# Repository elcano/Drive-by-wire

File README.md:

# DriveByWire

Obsolete. New code is in DBW version 5.

This repository is for use with the **Drive by Wire** board created to be used for the ELCANO self-driving tricycle. In order for this module to run external libraries are required.

Repositories were updated 6/8/2023 but clobbered previous history. Chief addition is use of an RC controller that allows manual control of throttle, brakes and steering.
The Sender files are intended for use on the Hi-Level board and do not really belong in the Drive-by-wire repository.

Libraries needed are listed below:

ALL Versions ________________________________
* PID by Brett Beauregard
    https://github.com/br3ttb/Arduino-PID-Library
    A simple controller calculator (proportional integral derivative) to calculate the error between a desired output and an actual output. Has files **PID_v1**

Version 3 (Arduino Mega) ________________________________
* CAN_BUS_SHIELD by Seeed-Studio
    https://github.com/Seeed-Studio/CAN_BUS_Shield
    Contains CAN_BUS communication protocols and required files such as **mcp_can** and **can-serial**

* Pin Change Interrupt by Nico Hood
    https://github.com/NicoHood/PinChangeInterrupt
    For custom configuration of Arduino pin properties. Has files **PinChangeInterupt**

* MCP48x2 DAC by Jonas Forsberg
    https://github.com/SweBarre/MCP48x2.
    Library for Digital to anolog converter. Has files **MCP48x2**

Version 4 (Arduino Due)  _______________________________________________
* Due CAN and CAN Common by Collin Kidder
    https://github.com/collin80/due_can
    https://github.com/collin80/can_common

## To Install

* Download the **Drive_By_Wire** module into the project parent directory
```
git clone https://github.com/elcano/Drive-by-wire.git
```
* Move into the **Drive_By_Wire** folder
```
cd Drive_By_Wire
```
* Download the required libraries
```
git clone https://github.com/Seeed-Studio/Seeed_Arduino_CAN.git
git clone https://github.com/br3ttb/Arduino-PID-Library.git
git clone https://github.com/NicoHood/PinChangeInterrupt.git
git clone https://github.com/SweBarre/MCP48x2.git
git clone https://github.com/ivanseidel/DueTimer.git
git clone https://github.com/collin80/can_common.git
git clone https://github.com/collin80/due_can.git
```
* Add the folders above to the IDE directory. In Windows, add the required libraries to: C:\Users\<username>\Documents\Arduino\libraries
* Arduino Due requires additional installation. On the IDE, go to Tools -> Boards -> Boards Manager -> Arduino SAM Boards (32-bits ARM Cortex-M3) 

## Navigating Arduino IDE: 
* **Selecting Board:** Tools -> Board -> Arduino AVR/SAM Boards -> Arduino Mega/Due
* **Selecting Serial Port:** Tools -> Port -> COM (Arduino Mega/Due)
* **Accessing Serial Monitor:** Right-hand Corner -> Select Baud Rate (115200)

## Drive-by-Wire: 
* **Low-level board code with RC control support with existing code for brakes, steering, and throttle.** 

## Test: 
* **Low-level board code with three functions to test each subsystems individually (brakes, steering, throttle).** 
* testBrake(): Activates brakes with 24V via Stop(), Holds brakes with 12V after 800ms via Update(), Releases brakes every ~2 seconds.
* testThrottle(): Gradually increases speed and decreases speed on DACA.
* testSteering(): Changes directions every 3 seconds, moving the linear actuator. 

## Sender: 
* **High-level board code to communicate with low-level board using CAN communication.** 
* Arguments for Function: Each data is reserved for 2 bytes. 
    *   currentSpeed: Controls the speed via the DACA, input: (0 -255).
    *   currentBrake: Apply and updates brakes if necessary, input: (0 - releases brakes, anything above 0 - applies brakes).
    *   currentAngle: Changes direction based on input (may need to calibrate based on sensors), left: 779 (1ms), middle: 722 (1.5ms), right: 639 (1.85ms).

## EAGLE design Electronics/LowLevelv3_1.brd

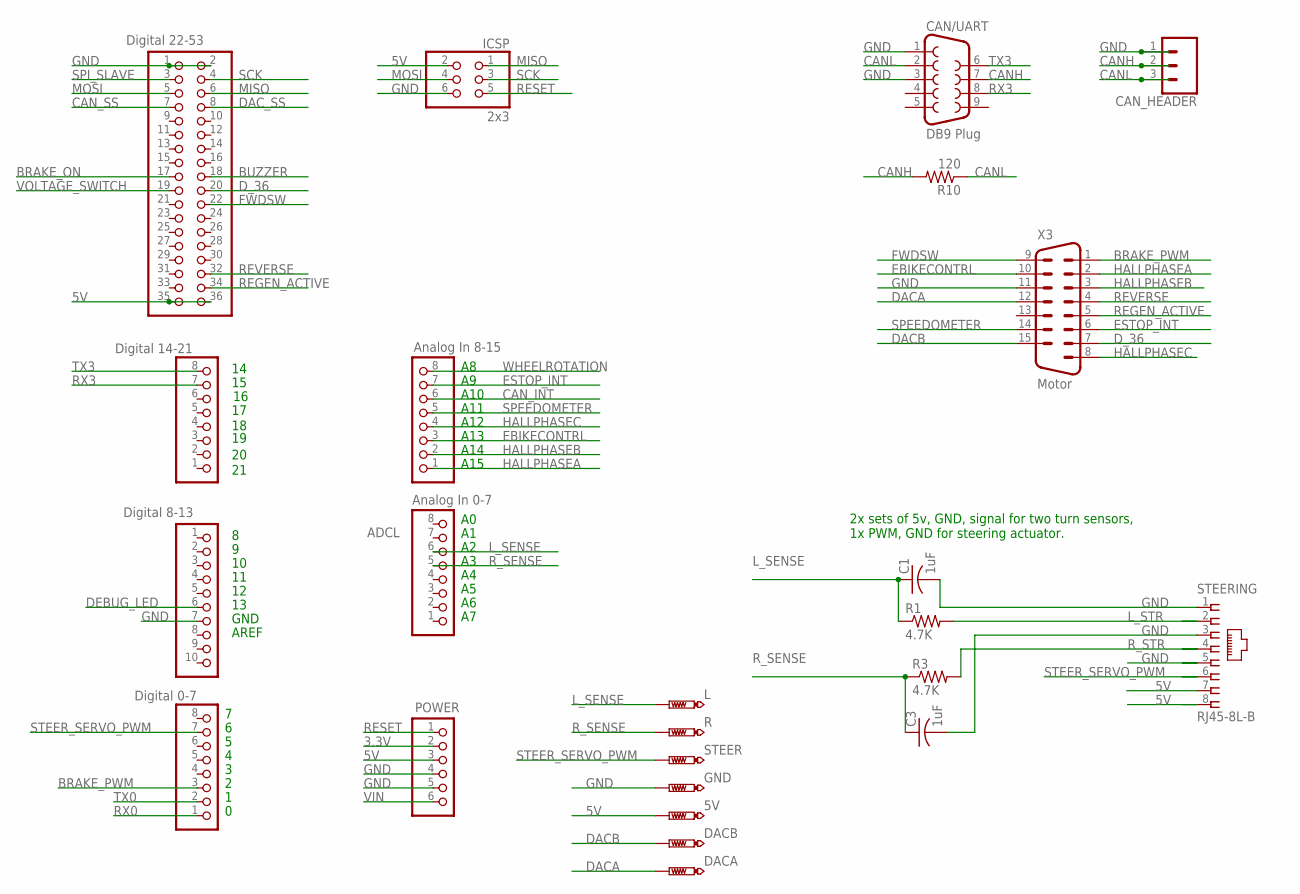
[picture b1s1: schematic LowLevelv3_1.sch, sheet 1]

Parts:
5V: PTR1PAD1-17; P1-17
ADCH: Analog In 8-15; 1X08
ADCL: Analog In 0-7; 1X08
C1, C3: 1uF; C1206
CAN/UART: DB9 Plug; DB9
CAN_HEADER: CONN_03-SCREW-5MM; SCREWTERMINAL-5MM-3
DACA: PTR1PAD1-17; P1-17
DACB: PTR1PAD1-17; P1-17
DIGITAL_0-7: Digital 0-7; 1X08
DIGITAL_8-13: Digital 8-13; 1X10
DIGITAL_14-21: Digital 14-21; 1X08
GND: PTR1PAD1-17; P1-17
ICSP: 2x3; 2X03
L: PTR1PAD1-17; P1-17
MEGA_EXPANSION: Digital 22-53; PINHEAD_2X18
POWER: PINHD-1X6; 1X06
R: PTR1PAD1-17; P1-17
R1, R3: 4.7K; R1206
R10: 120; R1206
STEER: PTR1PAD1-17; P1-17
STEERING: RJ45-8L-B; RJ45-NO-SHIELD
X3: Motor; 182-015-MALE

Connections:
3.3V: POWER.2
5V: 5V.TP, ICSP.2, MEGA_EXPANSION.35, MEGA_EXPANSION.36, POWER.3, STEERING.7, STEERING.8; also elsewhere on the board
BRAKE_ON: MEGA_EXPANSION.17; also elsewhere on the board
BRAKE_PWM: DIGITAL_0-7.3, X3.1
BUZZER: MEGA_EXPANSION.18; also elsewhere on the board
CANH: CAN/UART.7, CAN_HEADER.2, R10.2; also elsewhere on the board
CANL: CAN/UART.2, CAN_HEADER.3, R10.1; also elsewhere on the board
CAN_INT: ADCH.6; also elsewhere on the board
CAN_SS: MEGA_EXPANSION.7; also elsewhere on the board
DACA: DACA.TP, X3.12; also elsewhere on the board
DACB: DACB.TP, X3.15; also elsewhere on the board
DAC_SS: MEGA_EXPANSION.8; also elsewhere on the board
DEBUG_LED: DIGITAL_8-13.6; also elsewhere on the board
D_36: MEGA_EXPANSION.20, X3.7
EBIKECONTRL: ADCH.3, X3.10
ESTOP_INT: ADCH.7, X3.6; also elsewhere on the board
FWDSW: MEGA_EXPANSION.22, X3.9
GND: C1.2, C3.2, CAN/UART.1, CAN/UART.3, CAN_HEADER.1, DIGITAL_8-13.7, GND.TP, ICSP.6, MEGA_EXPANSION.1, MEGA_EXPANSION.2, POWER.4, POWER.5, STEERING.1, STEERING.3, STEERING.5, X3.11; also elsewhere on the board
HALLPHASEA: ADCH.1, X3.2
HALLPHASEB: ADCH.2, X3.3
HALLPHASEC: ADCH.4, X3.8
L_SENSE: ADCL.6, C1.1, L.TP, R1.1
L_STR: R1.2, STEERING.2
MISO: ICSP.1, MEGA_EXPANSION.6; also elsewhere on the board
MOSI: ICSP.4, MEGA_EXPANSION.5; also elsewhere on the board
REGEN_ACTIVE: MEGA_EXPANSION.34, X3.5
RESET: ICSP.5, POWER.1; also elsewhere on the board
REVERSE: MEGA_EXPANSION.32, X3.4
RX0: DIGITAL_0-7.1
RX3: CAN/UART.8, DIGITAL_14-21.7
R_SENSE: ADCL.5, C3.1, R.TP, R3.1
R_STR: R3.2, STEERING.4
SCK: ICSP.3, MEGA_EXPANSION.4; also elsewhere on the board
SPEEDOMETER: ADCH.5, X3.14
SPI_SLAVE: MEGA_EXPANSION.3
STEER_SERVO_PWM: DIGITAL_0-7.7, STEER.TP, STEERING.6
TX0: DIGITAL_0-7.2
TX3: CAN/UART.6, DIGITAL_14-21.8
VIN: POWER.6
VOLTAGE_SWITCH: MEGA_EXPANSION.19; also elsewhere on the board
WHEELROTATION: ADCH.8; also elsewhere on the board

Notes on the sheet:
A10
A11
A12
A13
A14
A15
GND
AREF
2x sets of 5v, GND, signal for two turn sensors, 1x PWM, GND for steering actuator.

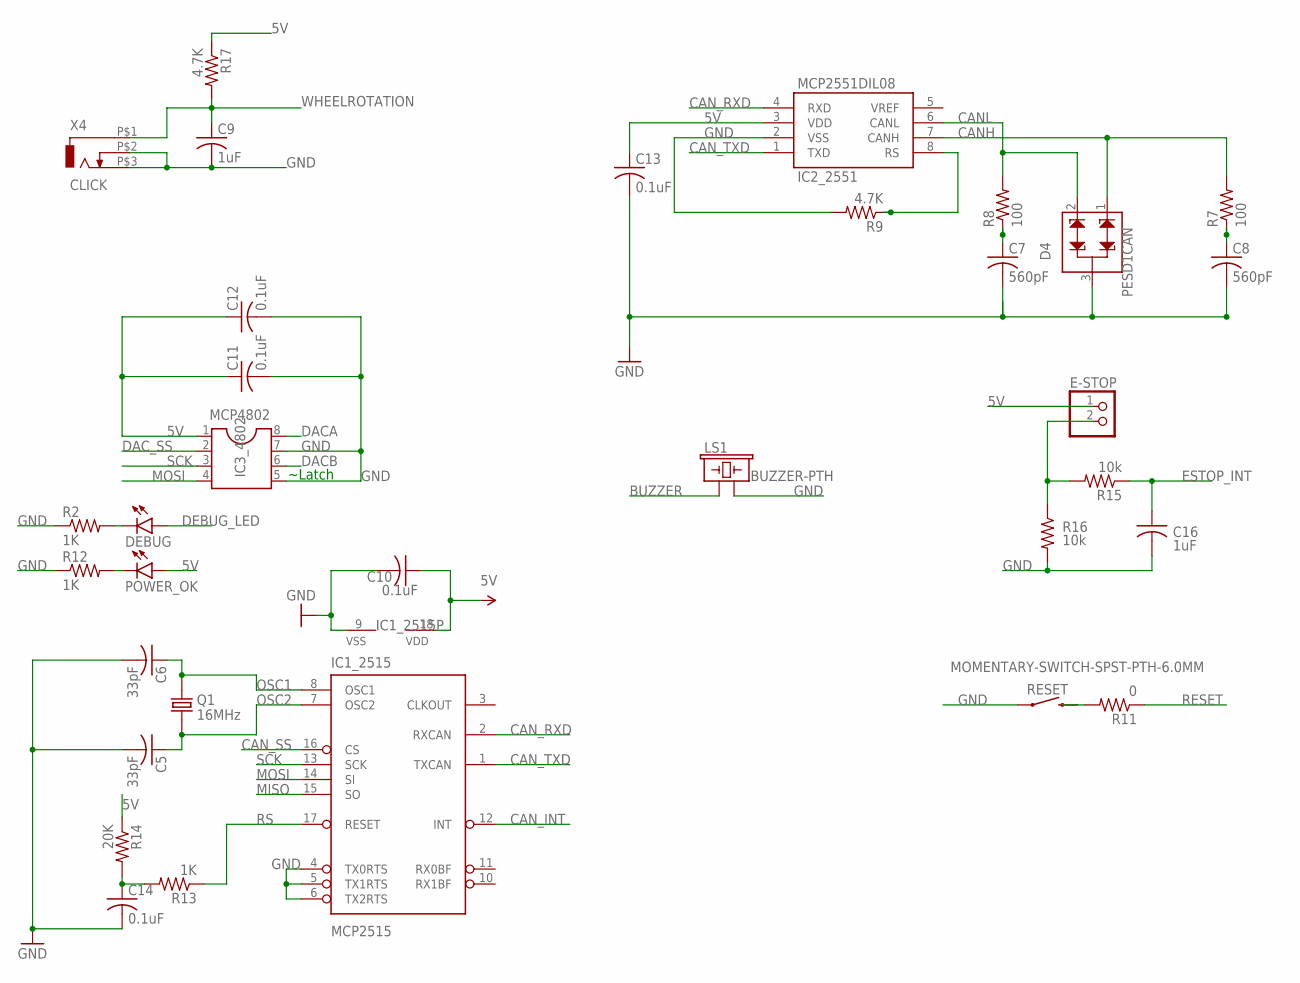
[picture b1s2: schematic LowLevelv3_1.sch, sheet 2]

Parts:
C5, C6: 33pF; C1206
C7, C8: 560pF; C1206
C9, C16: 1uF; C1206
C10, C11, C12, C13, C14: 0.1uF; C1206
D4: PESD1CAN; SPARKFUN-DISCRETESEMI_SOT23-3
DEBUG: LED3MM
E-STOP: PINHD-1X2; 1X02
IC1_2515: MCP2515; DIP18
IC2_2551: MCP2551DIL08; IC-PACKAGE_DIL08
IC3_4802: MCP4802; DIL08
LS1: BUZZER-PTH; BUZZER-12MM
POWER_OK: LED3MM
Q1: 16MHz; XTAL_ECS-160-20-46X
R2, R12, R13: 1K; R1206
R7, R8: 100; R1206
R9, R17: 4.7K; R1206
R11: 0; R1206
R14: 20K; R1206
R15, R16: 10k; R1206
RESET: MOMENTARY-SWITCH-SPST-PTH-6.0MM; TACTILE_SWITCH_PTH_6.0MM
X4: CLICK; ODO_JACK

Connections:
5V: C10.1, C11.1, C12.1, C13.1, E-STOP.1, IC1_2515.18 (VDD), IC2_2551.3 (VDD), IC3_4802.1, POWER_OK.A, R14.1, R17.1; also elsewhere on the board
BUZZER: LS1.+ (1); also elsewhere on the board
CANH: D4.1, IC2_2551.7 (CANH), R7.2; also elsewhere on the board
CANL: D4.2, IC2_2551.6 (CANL), R8.2; also elsewhere on the board
CAN_INT: IC1_2515.12 (INT); also elsewhere on the board
CAN_RXD: IC1_2515.2 (RXCAN), IC2_2551.4 (RXD)
CAN_SS: IC1_2515.16 (CS); also elsewhere on the board
CAN_TXD: IC1_2515.1 (TXCAN), IC2_2551.1 (TXD)
DACA: IC3_4802.8; also elsewhere on the board
DACB: IC3_4802.6; also elsewhere on the board
DAC_SS: IC3_4802.2; also elsewhere on the board
DEBUG_LED: DEBUG.A; also elsewhere on the board
ESTOP_INT: C16.1, R15.1; also elsewhere on the board
GND: C5.2, C6.2, C7.2, C8.2, C9.2, C10.2, C11.2, C12.2, C13.2, C14.2, C16.2, D4.3, IC1_2515.4 (TX0RTS), IC1_2515.5 (TX1RTS), IC1_2515.6 (TX2RTS), IC1_2515.9 (VSS), IC2_2551.2 (VSS), IC3_4802.5, IC3_4802.7, LS1.- (2), R2.1, R9.2, R12.1, R16.2, RESET.1, X4.P$2 (2), X4.P$3 (3); also elsewhere on the board
MISO: IC1_2515.15 (SO); also elsewhere on the board
MOSI: IC1_2515.14 (SI), IC3_4802.4; also elsewhere on the board
unnamed: R11.2, RESET.3 (2)
unnamed: C14.1, R13.2, R14.2
unnamed: DEBUG.K (C), R2.2
unnamed: E-STOP.2, R15.2, R16.1
unnamed: C7.1, R8.1
unnamed: C8.1, R7.1
unnamed: POWER_OK.K (C), R12.2
unnamed: IC2_2551.8 (RS), R9.1
OSC1: C6.1, IC1_2515.8 (OSC1), Q1.2
OSC2: C5.1, IC1_2515.7 (OSC2), Q1.1
RESET: R11.1; also elsewhere on the board
RS: IC1_2515.17 (RESET), R13.1
SCK: IC1_2515.13 (SCK), IC3_4802.3; also elsewhere on the board
WHEELROTATION: C9.1, R17.2, X4.P$1 (1); also elsewhere on the board

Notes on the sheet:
~Latch

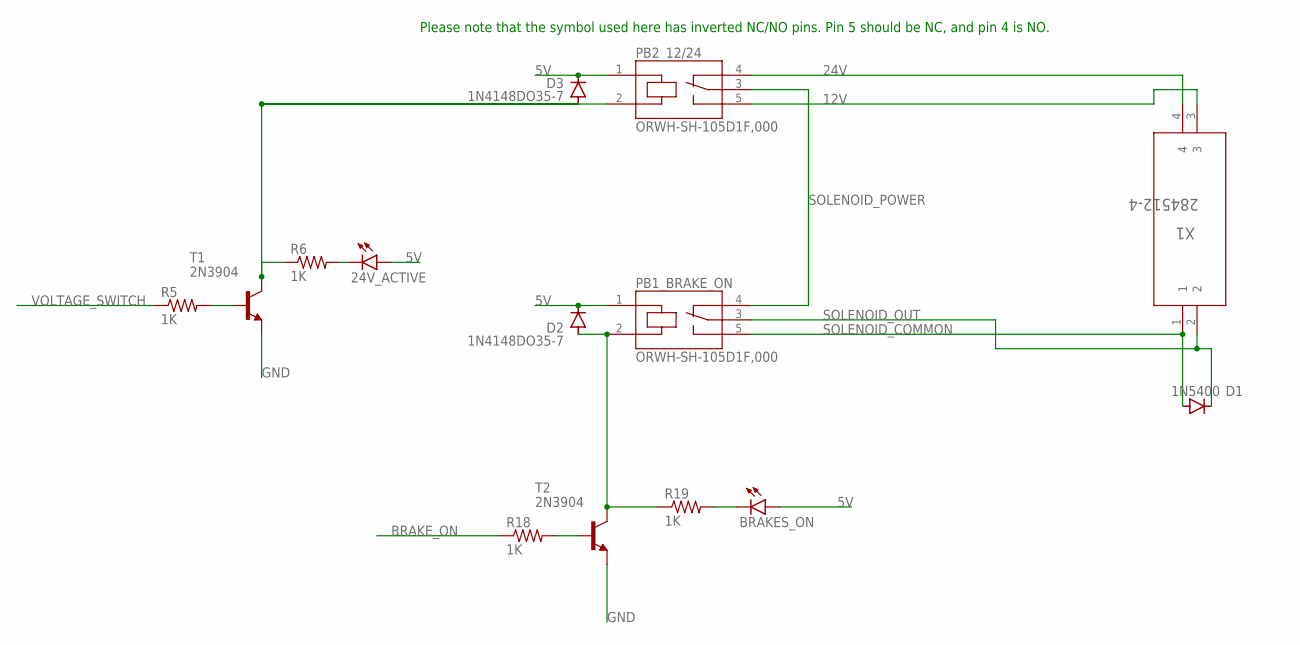
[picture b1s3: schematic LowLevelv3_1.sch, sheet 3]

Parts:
24V_ACTIVE: LED3MM
BRAKES_ON: LED3MM
D1: 1N5400; DO201-15
D2, D3: 1N4148DO35-7; DO35-7
PB1_BRAKE_ON, PB2_12/24: ORWH-SH-105D1F,000; TE_ORWH-SH-105D1F,000
R5, R6, R18, R19: 1K; R1206
T1, T2: 2N3904; TO92
X1: 284512-4

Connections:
5V: 24V_ACTIVE.A, BRAKES_ON.A, D2.C, D3.C, PB1_BRAKE_ON.1 (C1), PB2_12/24.1 (C1); also elsewhere on the board
12V: PB2_12/24.5 (NO), X1.3
24V: PB2_12/24.4 (NC), X1.4
BRAKE_ON: R18.1; also elsewhere on the board
GND: T1.3 (E), T2.3 (E); also elsewhere on the board
unnamed: R5.2, T1.2 (B)
unnamed: D3.A, PB2_12/24.2 (C2), R6.1, T1.1 (C)
unnamed: 24V_ACTIVE.K (C), R6.2
unnamed: R18.2, T2.2 (B)
unnamed: D2.A, PB1_BRAKE_ON.2 (C2), R19.1, T2.1 (C)
unnamed: BRAKES_ON.K (C), R19.2
SOLENOID_COMMON: D1.A, PB1_BRAKE_ON.5 (NO), X1.1
SOLENOID_OUT: D1.C, PB1_BRAKE_ON.3 (C), X1.2
SOLENOID_POWER: PB1_BRAKE_ON.4 (NC), PB2_12/24.3 (C)
VOLTAGE_SWITCH: R5.1; also elsewhere on the board

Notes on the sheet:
Please note that the symbol used here has inverted NC/NO pins. Pin 5 should be NC, and pin 4 is NO.

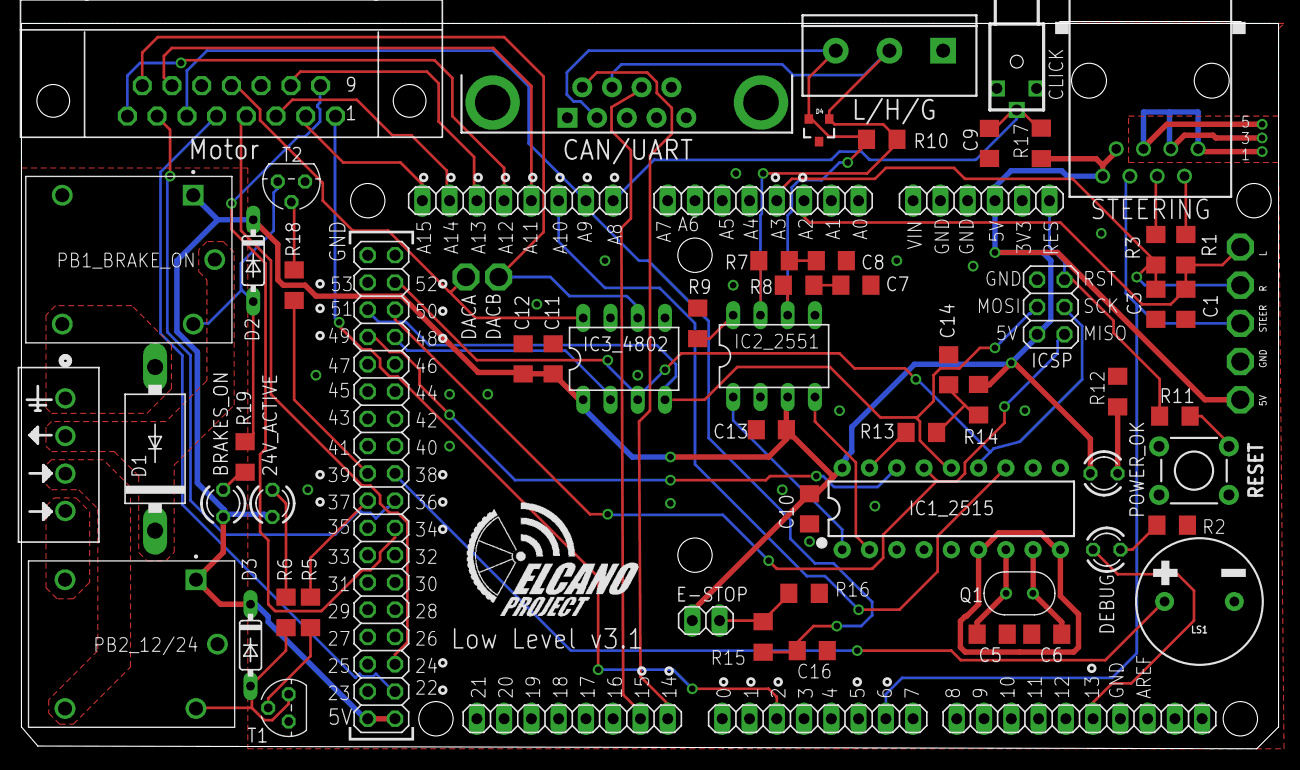
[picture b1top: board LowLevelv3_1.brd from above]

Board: 2 copper layers, 117.1 x 67.7 mm, 71 parts (0 on the bottom side), 60 nets.

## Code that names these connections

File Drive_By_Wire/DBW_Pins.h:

#ifndef _DBW_PINS_
#define _DBW_PINS_

#define DEBUG false
#define USE_PIDS false // throttle currently uses a PID controller, Steering does not current use a PID controller

#include <Arduino.h>

//Version can be 1,3 or 4; LLB = Low Level Board = Drive By Wire
#define DBWversion 4

/*---------- Version 1 - No Longer supported------------------------
#if DBWversion == 1
//Wheel click interrupt
#define IRPT_WHEEL         3
#define STEER_OUT_PIN      5
#define STEER_ON           8
#define BrakeVoltPin       9
#define BrakeOnPin        10
#define SelectAB          53
#define SelectCD          49
#define DAC_CHANNEL        0
#define AngleSensorLeft   A2
#define AngleSensorRight  A3
*/
/*---------- Version 3: Arduino Mega -------------------------------------*/
#if DBWversion < 4

/* Pin declarations */
// Serial Monitor uses pins 0,1 for RX0,TX0
// Servo to control the brakes; not used

#define BRAKE_PULSE_PIN     2
 // keep-alive watchdog is not yet implemented
#define WATCHDOG_PIN        5  
// Pin used to steer the vehicle with a pulse
#define STEER_PULSE_PIN     6
// Relay that turns on power to the steering system
#define STEER_ON_PIN        8
// Wheel angle sensors mounted on left and right steering columns
#define L_SENSE_PIN    A2
#define R_SENSE_PIN    A3

// Command to e-bike controller to use regenerative braking; not used 
#define REGEN_PIN          22
// Command to e-bike controller to drive in reverse; not used
#define REVERSE_PIN        24
// Switch to drive in forward or reverse; not used
#define FWDSW_PIN          34
#define D_36_PIN           36  // Not used
// Brakes, have relays for both on/off as well as selecting 12/24v power.
#define BrakeVoltPin       37
#define BUZZER_PIN         38  // Not used
#define BrakeOnPin         39

// CANbus slave select
#define CAN_SS_PIN         49  
// SPI chip select for DAC slave select. Channel A is for throttle
#define DAC_SS_PIN         48 
// we only use channel A for the throttle. B is routed but unused.
#define DAC_CHANNEL         0   
// Pins 51,52,53 are MISO, MOSI, SCK.
// originally intended as a return ground, these analog pins are free and on the steering header.
// Intent was to use L_SENSE - L_RTN as a differential signal.
//#define L_RTN_PIN        A6
//#define R_RTN_PIN        A7

/* Signals A8 through A15 are digital interrupts */
/* The Arduino Mega only has 6 interrupts, but an additional 8 can be added through the port pin change interrupt. */
//Wheel click interrupt (digitally high or low, referred to as an "odometer"). Once per wheel revolution.
// IRPT_WHEEL = WHEELROTATION
#define IRPT_WHEEL         A8
// physical E-Stop port; not used
#define IRPT_ESTOP_PIN     A9 
// Interrupt for can msg; not used
#define IRPT_CAN_PIN       A10 

// motor hall phases occur multiple times per wheel revolution
// A future design may make use of these for more precise speed feedback.
// The speedometer_pin would be jumpered to the signal in use
//Not implemented
#define SPEEDOMETER_PIN    A11
#define IRPT_PHASE_C       A12
#define EBIKE_POWER_IN_PIN A13
#define IRPT_PHASE_B       A14
#define IRPT_PHASE_A       A15


/*---------- Version 4: Arduino Due -------------------------------------*/
#else // DBWversion >=4

// Serial Monitor uses pins 0,1 for RX0,TX0
// Pins D0-D13 and A0-A5 are reserved for the Motor Shield
// The shield may block access to A6 and A7.
/*
 *  --------Motor shield pins --------------
 *  Channel A Current sensing   A0
 *  Channel B Current sensing   A1
 *  In2 Connector               A2
 *  In3 Connector               A3
 *  Channel A Speed (PWM)       3
 *  Out5 connector              5
 *  Out6 connector              6
 *  Channel B Brake             8
 *  Channel A Brake             9
 *  Channel B Speed (PWM)       11
 *  Channel A Direection        12
 *  Channel B Direection        13
 *  
 *  Version 4 connectors:
 *  RJ45 Steering: 
 *        L_RTN, L_SENSE, GND, 5V, STEER_PULSE, GND, R_RTN, R_SENSE, GND, 5V
 *  Two 4 wire screw terminals for CAN bus
 *        12V in, GND, CAN LO, CAN HI
 *  One 4 wire screw terminal for brake solenoid
 *        12V in, GND, 24V in, Brake solenoid out (12 or 24V)
 *        The 12V in on this connector is tied to the 12V in on the CAN bus connector,
 *        There should be only one connector to 12V power in, 
 *        A spare 12V connector could be wired to the motor shield, which
 *        already has a common ground.`
 *  One 4 wire screw terminal:
 *        12V out (controlled by STEER_ON), GND, IRPT_WHEEL, GND
 *  RJ45 to e-bike Motor Controller:
 *        FWDSW, EBIKE_POWER_IN, GND, DAC0, DAC1, SPEEDOMETER, WATCHDOG, 
 *        BRAKE_PULSE, REVERSE, REGEN, 

 */

// Wheel angles sensors mounted on left and right steering columns
#define L_SENSE_PIN        A10
#define R_SENSE_PIN        A11
// originally intended as a return ground, these analog pins are free and on the steering header.
// Intent was to use L_SENSE - L_RTN as a differential signal.
//#define L_RTN_PIN          26
//#define R_RTN_PIN          27

//----NEWLY ADDED PINs 6/8/25-----
#define THROTTLE_BR_CH2_PIN 9
#define STEERING_CH1_PIN 8

#define DRIVE_MODE_CH4_PIN 11
#define RC_CH3_ESTOP 10
#define RIGHT_TURN_PIN 29
#define LEFT_TURN_PIN 27

// Command to e-bike controller to use regenerative braking; not used 
#define REGEN_PIN           22
// The odd numbered pins from 23 to 39 are unassigned.

// Command to e-bike controller to drive in reverse; not used
#define REVERSE_PIN         24
// Pin used to steer the vehicle with a pulse
#define STEER_PULSE_PIN     26
// Relay that turns on power to the steering system
#define STEER_ON_PIN        4
// Debug or status for DBW
#define DBW_LED             30
 // keep-alive watchdog is not yet implemented
#define WATCHDOG_PIN        32  
// Pins 34 and 35 could conflict with the Router board on the Bridge.
// Switch to drive in forward or reverse; not used
#define FWDSW_PIN          36
#define BUZZER_PIN         38  // Not used
#define BrakeOnPin         39
// Brakes, have relays for both on/off as well as selecting 12/24v power.
#define BrakeVoltPin       40

// Servo to control the brakes; not used
#define BRAKE_PULSE_PIN    41
/* Signals D42-49 are digital interrupts */
/* If implemented on aa Arduino Mega, these are on Port L and can use pin change interrupt. */
/* Any Arduino Due pin can be an interrupt. */
// Interrupt for can msg; not used
#define IRPT_CAN_PIN       42
// Multiple clicks per wheel revolution (not implemented)
#define SPEEDOMETER_PIN    43
// When the E-bike controller has power, this line is 5V.
// If it falls to zero, ebike has lost power.
#define EBIKE_POWER_IN_PIN 45

// Wheel click interrupt (digitally high or low, referred to as an "odometer"). Once per wheel revolution.
// Odometer reed switch is pulled up to high voltage.
// IRPT_WHEEL = WHEELROTATION
#define IRPT_WHEEL         47
// DAC channel is he DAC address for throttle; not an Arduino pin.
#define DAC_CHANNEL         0   
/*------------ Dropped signals ------------------
 * The following signals have been dropped
// Motor hall phases occur multiple times per wheel revolution
// A future design may make use of these for more precise speed feedback.
// The speedometer_pin would be jumpered to the signal in use
   The three Hall Phases were never used: IRPT_PHASE_A, IRPT_PHASE_B, IRPT_PHASE_C
   If we use a signal from the hub motor, it will be on the SPEEDOMETER_PIN 

// physical E-Stop port; not used
  IRPT_ESTOP_PIN is not used. It was intended for a remote e-stop, but the
  e-stop now comes from the CAN bus.
  D_36_PIN    // Never used; intended as a spare signal
 -------------------------------------------------------------*/

// On the Due, SPI, CAN_SS and DAC_SS are not used. Use DAC0, DAC1, CANRX and CANTX  
// On Due MISO, MOSI, SCK are only on the ICSP, which is blocked by the motor shield.

#endif  // DBWversion 

#endif   //_DBW_PINS_

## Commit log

2019-12-04 Rename Elcano_C2_LowLevel_TimedBrakes.ino to TimedBrakes.ino
2019-12-04 Rename Elcano_C2_LowLevel.ino to Drive_ByWire.ino
2019-12-04 Rename Drive_ByWire.ino to Drive_By_Wire.ino
2020-04-24 just a test comment
2020-04-24 comment
2020-05-12 Moving library files to compile --> TODO: Consolidate libraries after linking HL/LL/RTR Arduino systems back together
2020-05-12 Updating readme to include needed libraries
2020-05-22 Fixed #include in vehicle.cpp so the sketch will compile
2020-05-31 CAN Message update
    Corrected CAN message parsing
    Corrected angle mapping for CAN message.
2020-08-01 Added DBW_Pins.h
2020-08-03 added Version 4 signals to DBW_Pins.h
2020-08-14 Updated V4 pin numbers; changes for Due
2020-10-31 convert mcp_can methods to due_can / can_common
2020-10-31 Add due conversion for sending CAN messages
2020-10-31 Update code to remove TODO comments and clean up Due conversion code
2020-10-31 Add preprocessor command to mega library
2020-11-20 Clean up comments on vehicle.h
2021-05-25 Updated install instructions for Drive_By_Wire module
2023-03-07 add modified files and updated README.md
2023-06-08 First half 2023 changes
2023-07-01 Update and rename Settings.h to SettingsTemplate.h
    Download SettingsTemplate.h, and save it as your own Settings.h. Settings.h does not belong in the repository.
2023-07-01 Settings.h replaced by SettingsTemplate.h and comments added
2023-07-01 Settings.h replaced by SettingsTemplate.h
    Comments added. Redundant includes dropped from vehicles.cpp. Added gitignore
2023-07-01 Removed code from Settings.h
    Get the real stuff from SettingsTemplate.h
2023-07-03 Removed undocumented TESTING
    Renamed LLBversion to DBWversion; set USE_PIDS true
2023-07-03 DBWversion checks Mega/Due
2023-07-05 Documented needed libraries
2023-07-05 Removed unneeded CAN files
    #include can*.h not used.
2024-04-15 New steering and data logging for steering
2024-04-20 Add files via upload
    Using left angle sensor instead of right angle sensor RC commands currently work.
2024-05-20 Datalogger and Steering Software Implemented
    PID controller is not used for Steering or throttle and CAN bus is disabled due to problem with board.
2024-06-24 Add files via upload
    Changed steering, throttle, brake, and RC controller to non static to fix the compilation error when using the Arduino Due
2024-07-11 GPS addition
    For the future version we are going to remove the GPS functionality and replace the current shield with a new logging shield that can interface with the Arduino due.
2024-07-12 Throttle produces correct outputs
2024-07-17 Brakes and Throttle verified
    Inverter option in brake.cpp set to true and throttle is set initially to max to get the wheel moving
2024-07-31 Data logger verified and takes the compile time if more recent
2025-03-15 Add files via upload
    This is the updated steering board for the Elcano Drive-by-wire system.
2025-03-17 added controlHBridge function
2025-06-08 Testing Changes
    Includes logging, brakes, throttle, etc
2025-06-09 Create CAN_Receiver
    This receiver code is used to test the Arduino DUE's ability to receive CAN messages using a transceiver. By default, this code sets a digital pin to high as a high-level confirmation that the CAN si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
2025-06-09 LowLevel V4.1 PCB Diagram KiCAD + Steering Board.
    These are all the KiCAD, EasyEDA, and LTspice files that our team has modified for DBW V4.1.
2025-06-09 changes
    changes
2025-06-09 Updated Changes (6/9/2025)
    Minor fixes
2025-06-09 changes now
    updates to brakes and vehicle
2025-06-09 Updated DBW V4.1 Pin mapping for LowLevel V4.1
    D27 is L_TN and D_29 is R_TN to better fit the operation of the dual steering signal Steering Board V4.1.
    Make any changes to any other signals when necessary. Leave R_TN and L_TN as is.
2025-06-09 3:30pm changes 6/9/25
    3:30pm changes 6/9/25
2025-06-11 Datalogger outputs of DBW V4.1 code.
    This ZIP archive contains LOG00-LOG21.csv.
2025-08-19 Create JetsonNano_Autonomous_DBW
    Python Algorithm for Autonomous Test Bench, includes speed sensor, GPS speed, waypoint input, CAN outputs
2026-05-07 README.md indicates DBW versions 1-4 is obsolete

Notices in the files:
parts and their libraries:
SparkFun-Connectors: Licensing: CC v3.0 Share-Alike You are welcome to use this library for commercial purposes.
SparkFun-IC-Comms: Licensing: Creative Commons ShareAlike 4.0 International - https://creativecommons.org/licenses/by-sa/4.0
